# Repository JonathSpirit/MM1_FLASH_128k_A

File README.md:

# MM1_FLASH_128k_A

Copyright (C) 2020 Guillaume Guillet\
Licensed under CERN-OHL-W v2 or later

<table border="0px">
<tr>
<td>
This source describes Open Hardware and is licensed under the CERN-OHL-W v2 or later.
</td>
</tr>
<tr>
<td>
You may redistribute and modify this documentation and make products
using it under the terms of the CERN-OHL-W v2 (https:/cern.ch/cern-ohl).
This documentation is distributed WITHOUT ANY EXPRESS OR IMPLIED
WARRANTY, INCLUDING OF MERCHANTABILITY, SATISFACTORY QUALITY
AND FITNESS FOR A PARTICULAR PURPOSE. Please see the CERN-OHL-W v2
for applicable conditions.
</td>
</tr>
</table>

Made with [Kicad](https://kicad.org/)

## Description
A FLASH card with 128kBytes of capacity and compatible with [MM1 standard](https://github.com/JonathSpirit/GComputer_standard).

## Status

Version :
> MM1_FLASH_128k_A revision 1

Status :
> Not tested !

Known issues :
> (Empty)

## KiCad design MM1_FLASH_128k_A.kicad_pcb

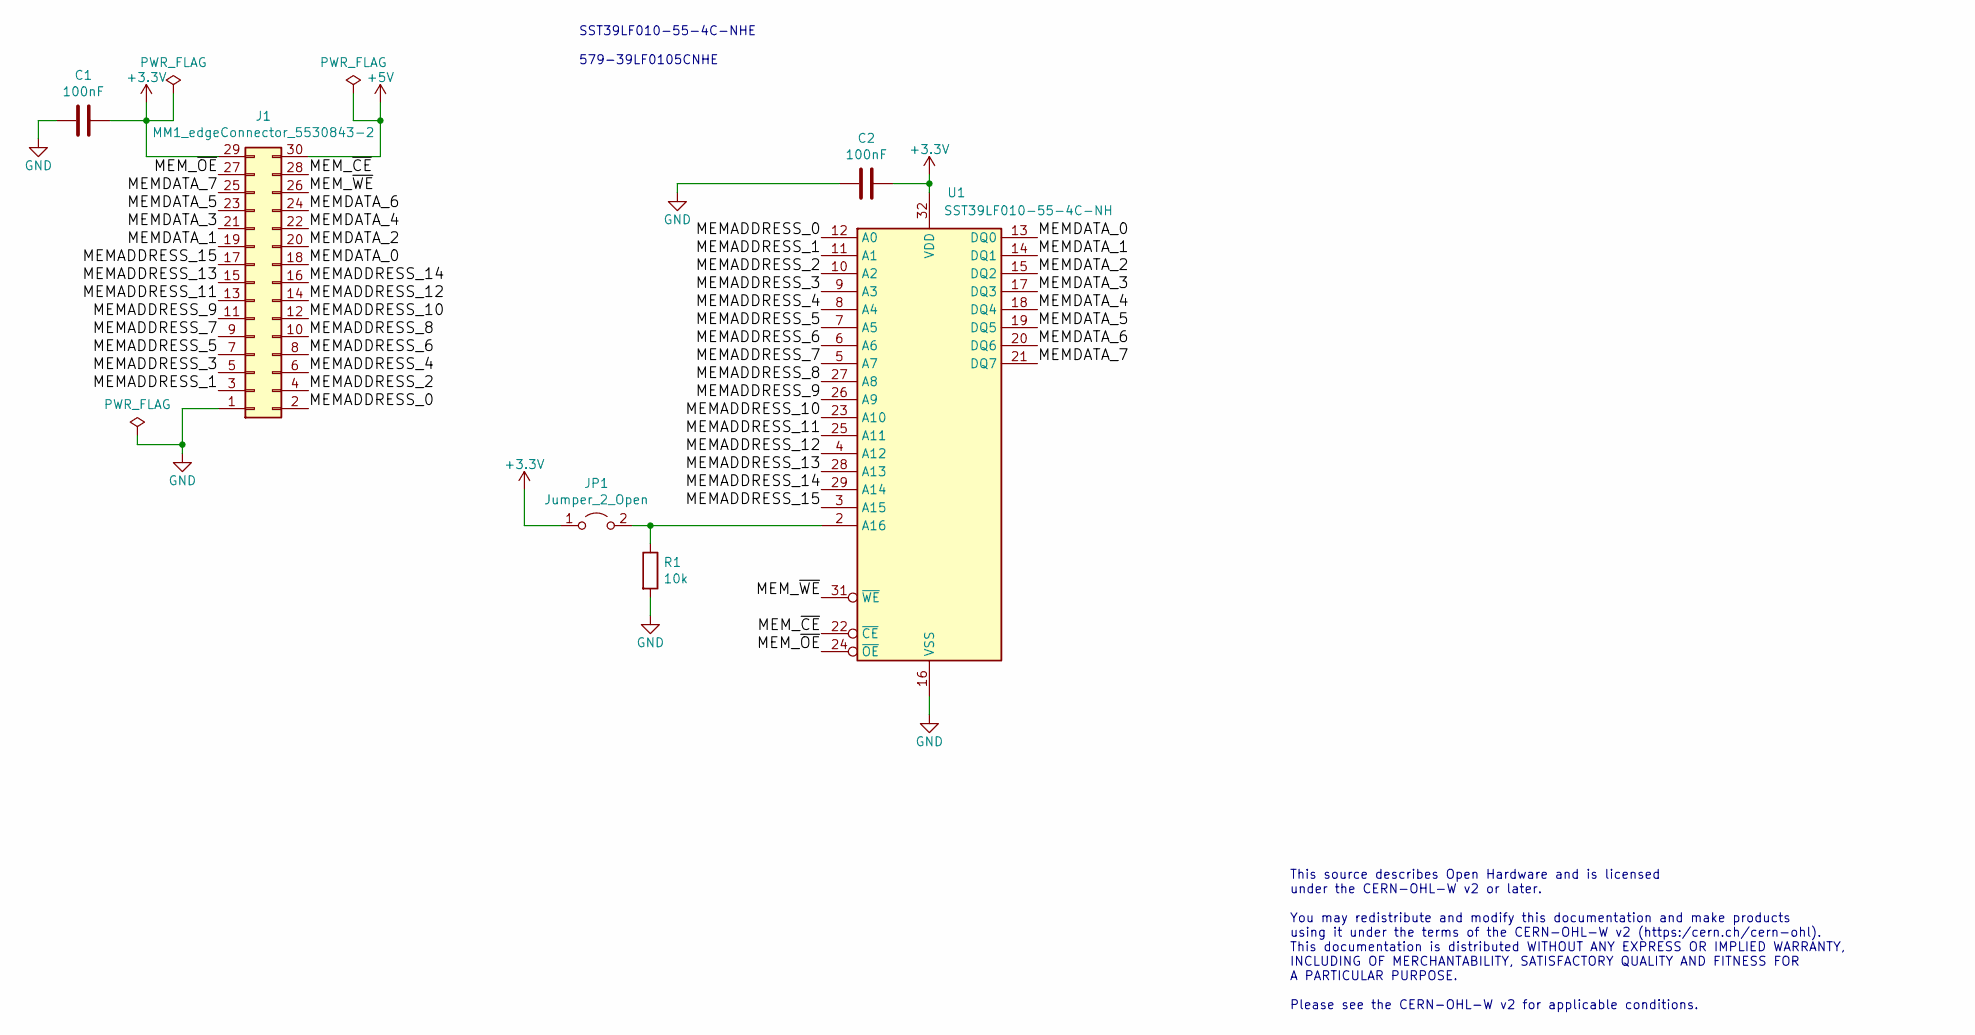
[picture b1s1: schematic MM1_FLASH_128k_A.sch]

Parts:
C1, C2: 100nF; C_0805_2012Metric
J1: MM1_edgeConnector_5530843-2; 5530843-2_edge
JP1: Jumper_2_Open; PinHeader_1x02_P2.54mm_Vertical
R1: 10k; R_0805_2012Metric
U1: SST39LF010-55-4C-NH; PLCC-32_THT-Socket

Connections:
+3V3: C1.2, C2.1, J1.29, JP1.1 (A), U1.32 (VDD)
+5V: J1.30
/MEMADDRESS_0: J1.2, U1.12 (A0)
/MEMADDRESS_1: J1.3, U1.11 (A1)
/MEMADDRESS_2: J1.4, U1.10 (A2)
/MEMADDRESS_3: J1.5, U1.9 (A3)
/MEMADDRESS_4: J1.6, U1.8 (A4)
/MEMADDRESS_5: J1.7, U1.7 (A5)
/MEMADDRESS_6: J1.8, U1.6 (A6)
/MEMADDRESS_7: J1.9, U1.5 (A7)
/MEMADDRESS_8: J1.10, U1.27 (A8)
/MEMADDRESS_9: J1.11, U1.26 (A9)
/MEMADDRESS_10: J1.12, U1.23 (A10)
/MEMADDRESS_11: J1.13, U1.25 (A11)
/MEMADDRESS_12: J1.14, U1.4 (A12)
/MEMADDRESS_13: J1.15, U1.28 (A13)
/MEMADDRESS_14: J1.16, U1.29 (A14)
/MEMADDRESS_15: J1.17, U1.3 (A15)
/MEMDATA_0: J1.18, U1.13 (DQ0)
/MEMDATA_1: J1.19, U1.14 (DQ1)
/MEMDATA_2: J1.20, U1.15 (DQ2)
/MEMDATA_3: J1.21, U1.17 (DQ3)
/MEMDATA_4: J1.22, U1.18 (DQ4)
/MEMDATA_5: J1.23, U1.19 (DQ5)
/MEMDATA_6: J1.24, U1.20 (DQ6)
/MEMDATA_7: J1.25, U1.21 (DQ7)
/MEM_~CE: J1.28, U1.22 (~CE)
/MEM_~OE: J1.27, U1.24 (~OE)
/MEM_~WE: J1.26, U1.31 (~WE)
GND: C1.1, C2.2, J1.1, R1.2, U1.16 (VSS)
unnamed: JP1.2 (B), R1.1, U1.2 (A16)

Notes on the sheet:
SST39LF010-55-4C-NHE 579-39LF0105CNHE
This source describes Open Hardware and is licensed under the CERN-OHL-W v2 or later. You may redistribute and modify this documentation and make products using it under the terms of the CERN-OHL-W v2 (https:/cern.ch/cern-ohl). This documentation is distributed WITHOUT ANY EXPRESS OR IMPLIED WARRAN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

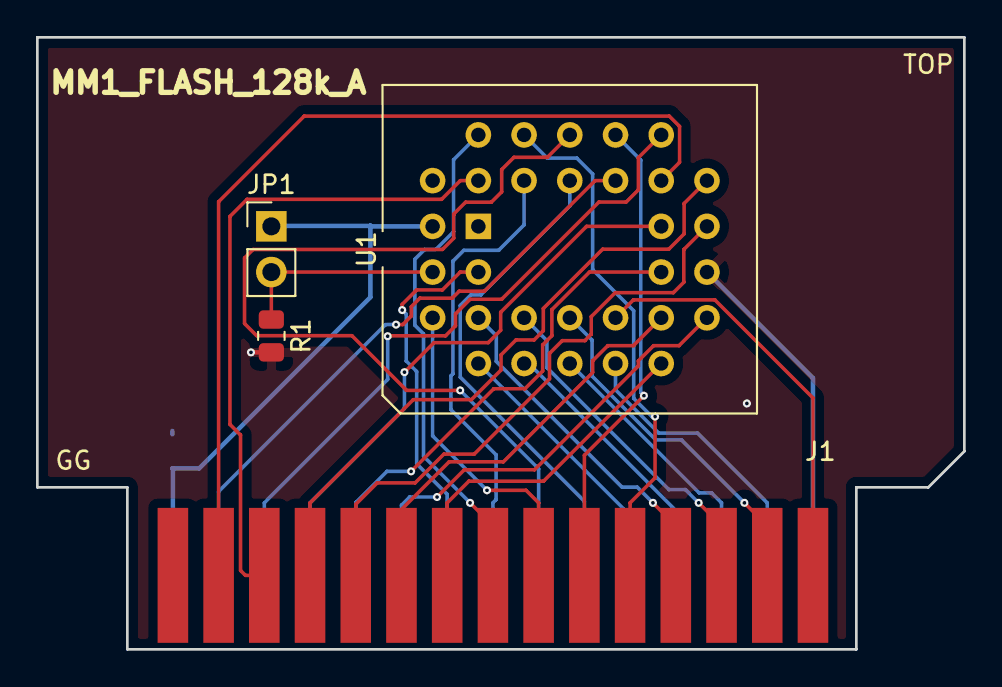
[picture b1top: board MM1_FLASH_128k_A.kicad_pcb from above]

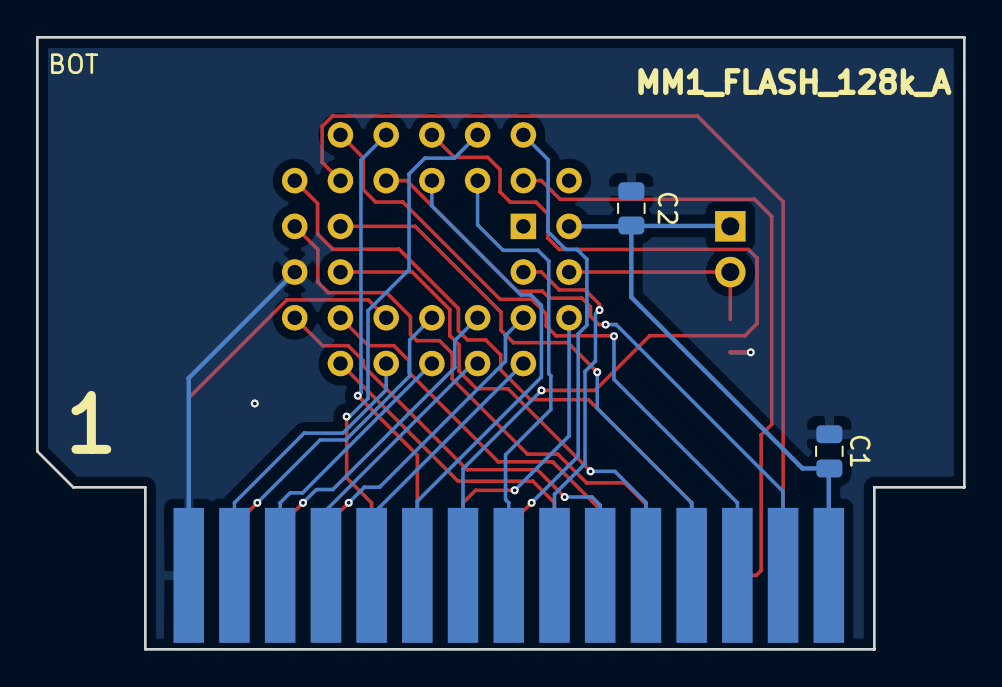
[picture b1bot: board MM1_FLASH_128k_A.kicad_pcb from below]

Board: 2 copper layers, 51.5 x 34.0 mm, 6 parts (2 on the bottom side), 30 nets.

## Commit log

2020-11-20 .gitignore file
2020-11-20 initial push
2020-11-23 materials, images
2020-11-23 Gerbert
2020-11-23 adding plcc-32 socket
2021-11-08 Update README.md
    https://forum.kicad.info/t/warning-avoid-all-links-to-kicad-pcb-org-use-kicad-org/31521

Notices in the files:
MM1_FLASH_128k_A.kicad_pcb:
Copyright Guillaume Guillet 2020
